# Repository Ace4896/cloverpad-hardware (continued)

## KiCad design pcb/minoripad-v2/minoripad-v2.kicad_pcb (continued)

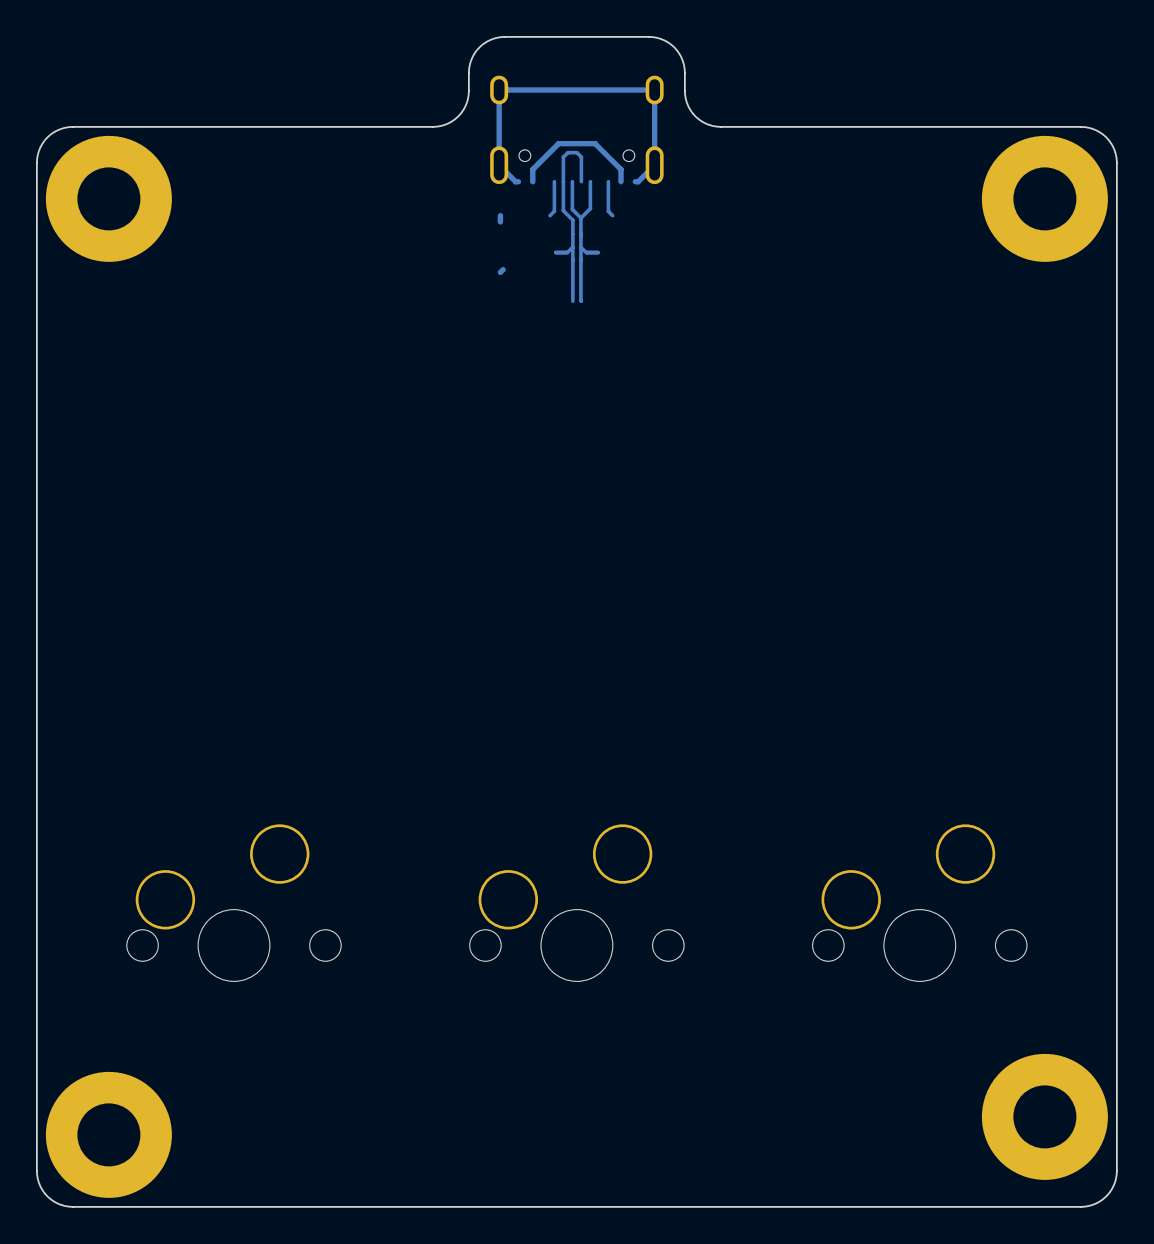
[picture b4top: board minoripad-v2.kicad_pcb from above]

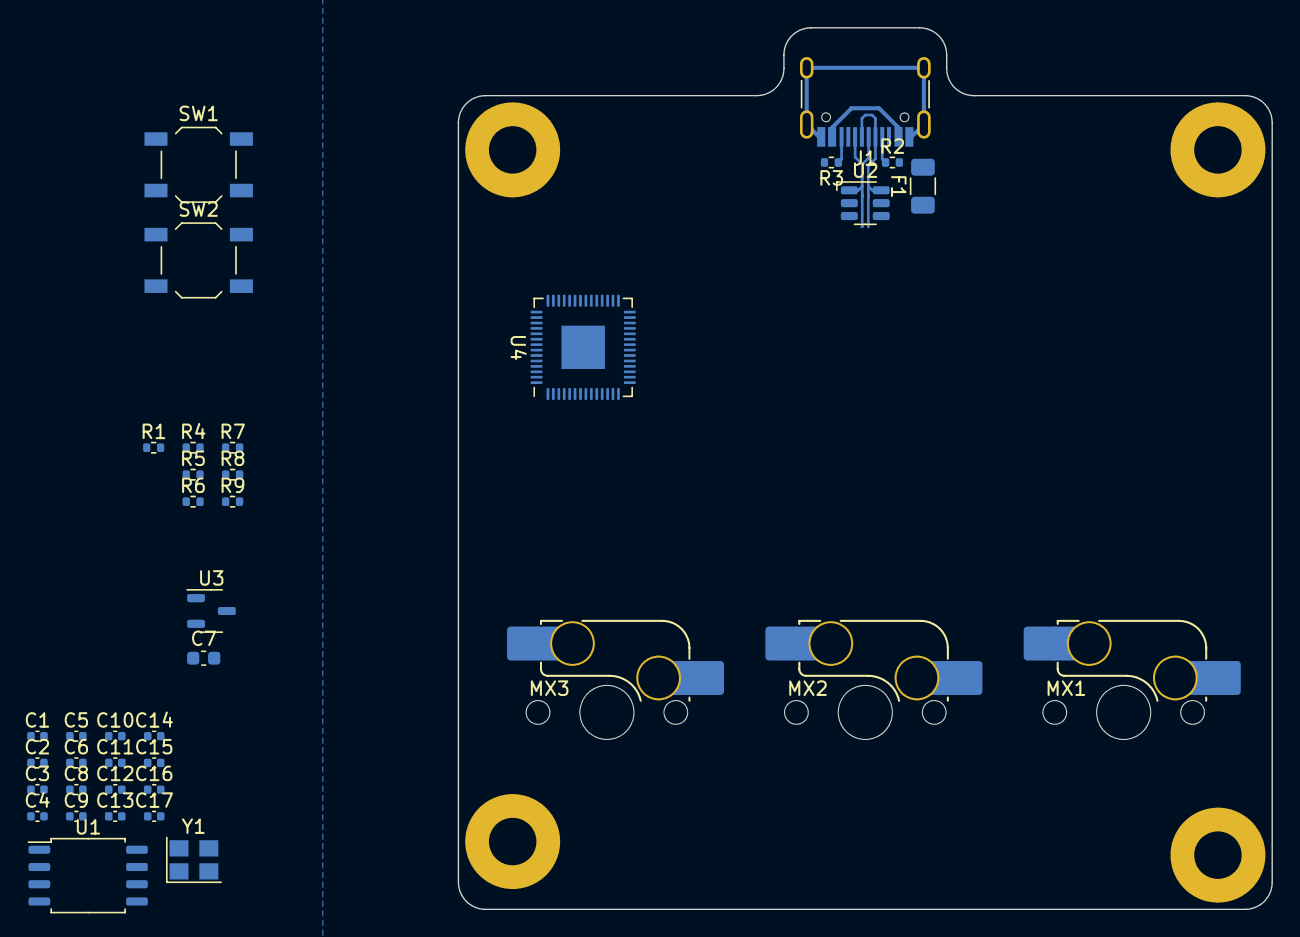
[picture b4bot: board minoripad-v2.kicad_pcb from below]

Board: 2 copper layers, 60.0 x 65.0 mm, 42 parts (42 on the bottom side), 26 nets.

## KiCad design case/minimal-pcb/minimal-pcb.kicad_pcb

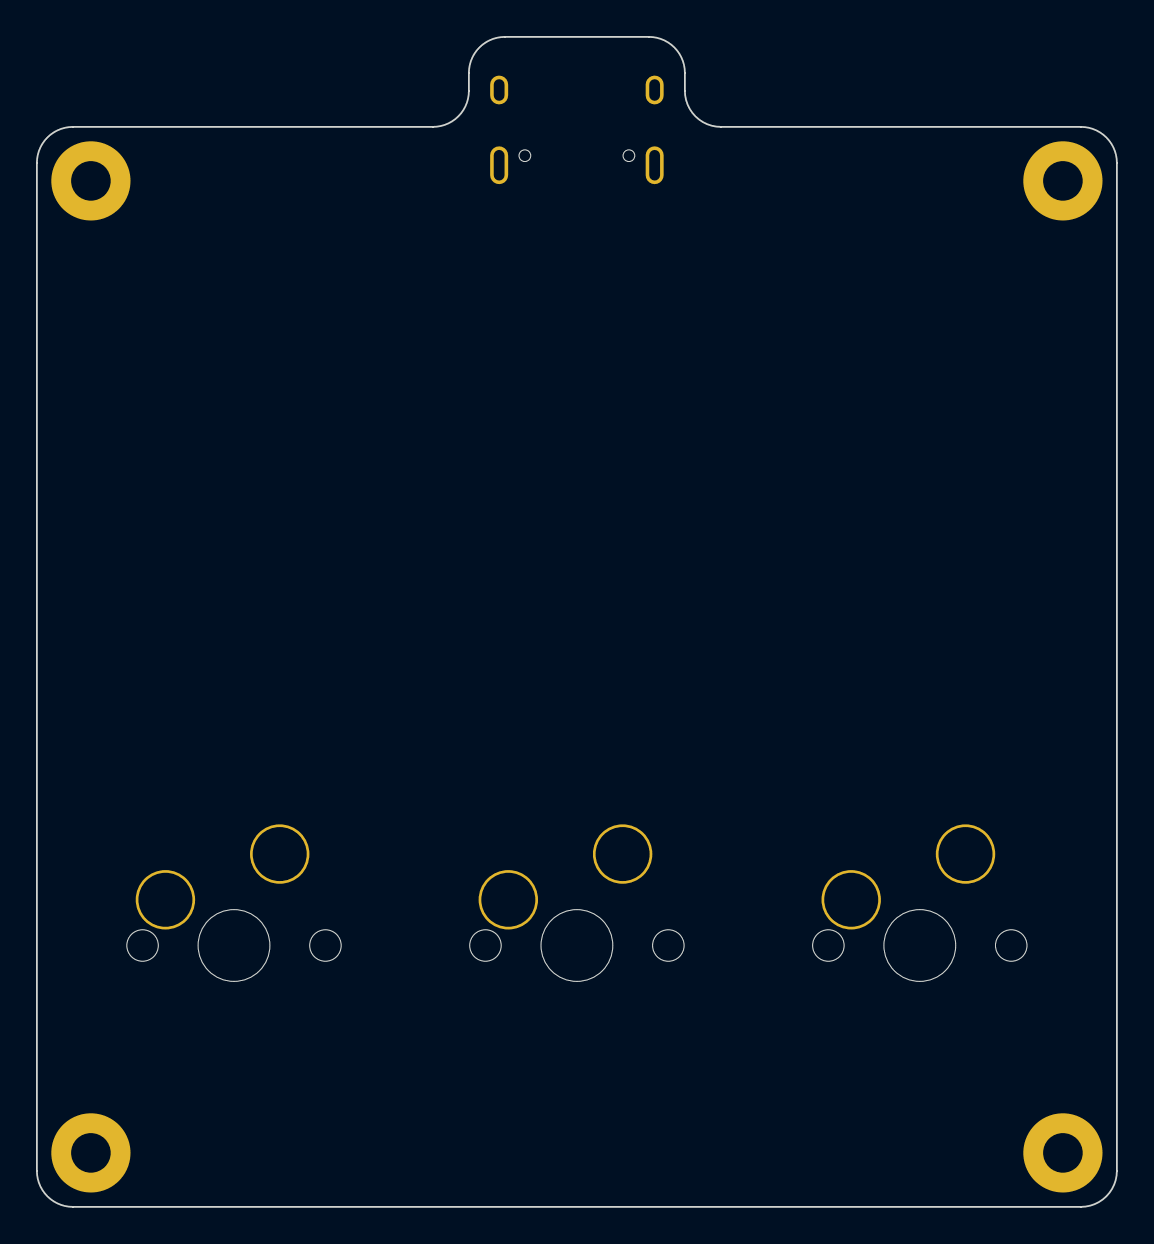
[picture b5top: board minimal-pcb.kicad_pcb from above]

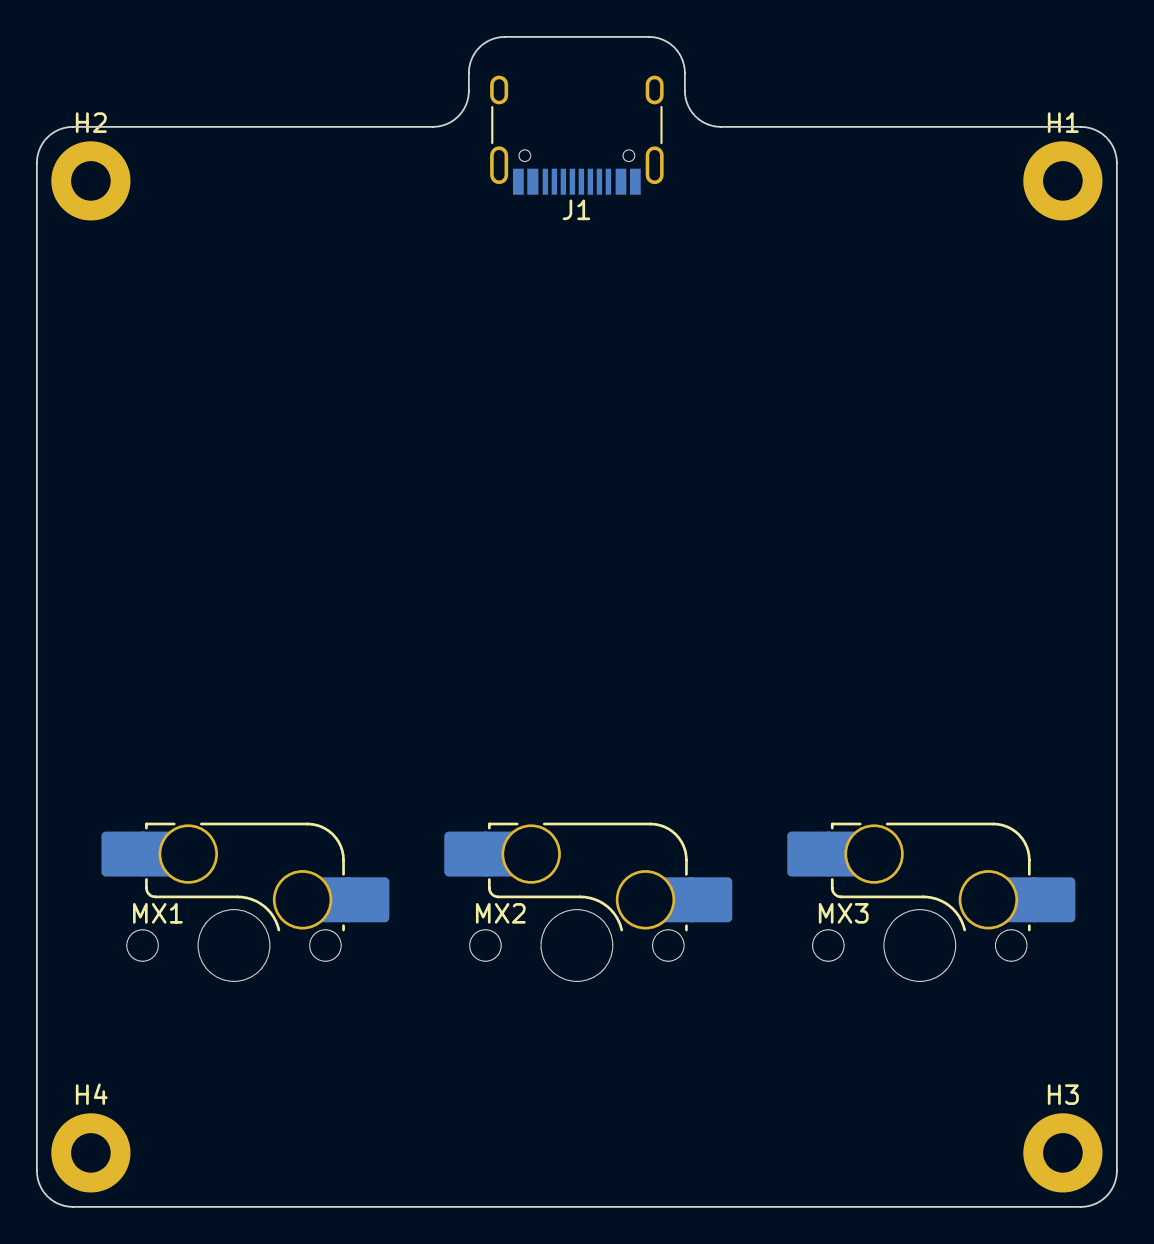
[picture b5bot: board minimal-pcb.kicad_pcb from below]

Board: 2 copper layers, 60.0 x 65.0 mm, 8 parts (8 on the bottom side), 2 nets, no tracks yet.

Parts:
H1, H2, H3, H4: Mounting Hole; MountingHole_2.2mm_M2_Pad
J1: USB_C_Receptacle_USB2.0; USB_C_Receptacle_HRO_TYPE-C-31-M-12
MX1, MX2, MX3: MX_SW_HS; SW_MX_HS_1u

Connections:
unnamed: J1.A1 (GND), J1.A12 (GND), J1.B1 (GND), J1.B12 (GND)
unnamed: J1.A4 (VBUS), J1.A9 (VBUS), J1.B4 (VBUS), J1.B9 (VBUS)

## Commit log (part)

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2023-11-05 feat: initial commit
2023-11-05 chore: add kle layout
2023-11-05 docs: add notes on lekker / ks-20 switches
2023-11-05 chore: setup kicad project for pcb
2023-11-05 docs: add datasheets for RP2040
2023-11-05 chore: add kicad symbols + footprints from previous attempt
2023-11-05 feat: initial schematic
    has the bare minimum components for a working keypad.
2023-11-05 chore: add auto saved files to gitignore
2023-11-05 feat: add rgb underglow
2023-11-05 refactor: use marbastlib footprint for in-switch LED
    to make it easier to align.
2023-11-05 feat: initial attempt at laying out pcb
    routing will be tricky - might need a 4 layer pcb due to the mixed voltages...
    probably better to remove the in-switch LEDs for the time being...
2023-11-06 docs: add labels for relevant parts
2023-11-06 fix: add 3.3v to 5v logic conversion
    this uses the 74AHCT1G125. there are values that can step up multiple pins at once, but it seems cheaper to just use individual ones. it should also be easier to route, as the logic level conversion 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
2023-11-06 feat: routing for rgb leds + logic level conversion
2023-11-07 feat: fully connected pcb
    ended up removing the debug header - I don't think these appear in production boards anyway, so should be OK.
    there's probably a better way to route the analog lines, but I couldn't come up with anything for it...
2023-11-07 feat: add m2 screw holes the footprint already takes the 4mm width of the standoffs into account, so should be OK as long as I position it correctly in CAD.
2023-11-07 chore: add title + revision to pcb design
2023-11-11 feat: add minimal pcb design for case measurements
2023-11-11 feat: export minimal pcb to step file
2023-11-11 refactor: use git submodules for mx switch 3d models (1/2)
2023-11-11 refactor: use git submodules for mx switch 3d models (2/2)
2023-11-11 docs: update README.md
2023-11-11 docs: reword repository layout
2023-11-11 fix: move switches slightly higher, to move away from screw holes
2023-11-11 docs: add the beginnings of a build guide
2023-11-11 refactor: drive switch LEDs from a single output pin
2023-11-12 feat: routing for new pcb required shuffling some components around, but this casn be accounted for in software, so it's not a big deal.
2023-11-12 refactor: re-route power and signals for switch LEDs
2023-11-13 docs: add ks-20 datasheet + notes on hall sensors
2023-11-13 feat: add haruka emote on back of pcb
2023-11-13 feat: add minori emote on front of pcb
2023-11-13 chore: add chosen emotes + splash art for pcb
2023-11-13 chore: trim source images for emotes
2023-11-13 feat: add mmj logo to front of pcb
2023-11-13 feat: wip attempt at vectorizing haruka emote
2023-11-14 chore: re-organise pcb artwork
2023-11-14 fix: fix haruka-16 emote on pcb and adjust alignment
2023-11-14 chore: remove pcb artwork for now since I want to try re-routing the PCB again.
2023-11-14 refactor: new pcb layout
    more compact and has fewer crossing lines. can definitely shrink the PCB, but I've picked this size so it's possible to see the design from the top.
2023-11-14 refactor: create custom footprint for KS-20 w/ DRV5056
    this includes a custom silkscreen, reference value and a rule area to disallow copper fills in the middle of the sensor.
2023-11-14 refactor: route +5v for underglow without crossing over analog lines
2023-11-15 chore: rename mounting holes in schematic
2023-11-15 refactor: route analog +3v3 without going underneath LEDs just realised that it may cause some noise in the supply.
2023-11-15 docs: fix typo
2023-11-15 fix: resolve all silkscreen overlaps
2023-11-15 fix: resolve footprint mismatch warnings
2023-11-15 chore: export 3d step file for pcb
    measurements look good; no issues with component clearance and the
    bottom cutouts line up with the buttons.
2023-11-15 refactor: use 1206 footprint for fuse
    there are more polyfuses with 500mA hold current at this size.
2023-11-15 feat: setup bom and initial gerbers files
2023-11-15 feat: setup jlcpcb tools
    seems to be working - the generated gerbers, bom and cpl are correct.
    the DRV5056 isn't being picked up, but it's likely just because it's out of stock.
2023-11-15 feat: add jlc order number placeholder
2023-11-15 fix: ensure that mounting holes are excluded from bom
2023-11-15 docs: fix typo in component table
2023-11-15 feat: add haruka-16 to pcb again
2023-11-15 fix: adjust linework on minori-02
2023-11-15 feat: add rest of mmj to front of pcb
2023-11-15 feat: add mmj logo to back of pcb
2023-11-15 docs: fix copy-paste error for kicad 7 link
2023-11-15 fix: add missing saved details
2023-11-16 fix: adjust ks-20 footprints so they're on front side by default
    so that when it's flipped, the components appear on the back side in the BOM. this way, it can be assembled with the rest of the components
2023-11-16 fix: convert case mounting holes to 3.5mm diameter hexagons
2023-11-16 docs: add note on hex standoff outer diameter
2023-11-17 refactor: parameterize hex standoff outer diameter
2023-11-17 docs: suggest frosted acrylic for plate
    to help the switch LED lighting diffuse a bit better.
2023-11-19 docs: fix quantity of m2 screws in build guide
2023-11-19 fix: rework clover in mmj logo
2023-11-19 chore: remove kle
    doesn't look like I'll need it - can always re-add it later.
2023-11-19 chore: re-organise folder structure
2023-11-19 docs: add link to assets folder
2023-11-20 docs: initial notes on determining magnet distance
2023-11-21 fix: another way of interpreting the ks-20 datasheet
    this gives a profile that is closer to that of the datasheet.
2023-11-21 feat: another attempt using fractional curve fitting
2023-11-21 chore: add plot titles
2023-11-28 fix: use padded 3.5mm mounting holes in minimal PCB
2023-11-28 chore: update 3d .step files for pcbs
2023-11-28 fix: use rounded 3.5mm mounting holes in case
    also use the new 3d models for the PCBs. nice to see that all of them line up now.
2023-11-28 fix: correct license for marbastlib
2023-11-28 docs: add copyright notice for MMJ
2023-11-28 docs: fix grammar in README
2023-11-28 fix: move JLC order number placeholder
    so it doesn't overlap with the pad.
2023-11-28 fix: remove remaining references to hex standoffs
2023-11-28 refactor: minify kle layout
    since this is the format that will be sent over the wire.
2023-11-28 fix: use k1, k2 and k3 in kle
    to make it more universal.
2023-11-28 fix: 0-based indexing
    to make it easier later...
2023-12-02 docs: update parts list to use DRV5056A4
2023-12-02 docs: update lcsc part number for DRV5056A4
2023-12-05 refactor: cleanup magnet-distance notebook
    makes it a bit easier to compare the different curve fits.
2023-12-22 chore: rename project
2023-12-22 feat: add minoripad
    this is a simplified version of the harukapad, with regular MX switches and no RGB effects.
    will be used to validate my case design.
2023-12-22 chore: import minoripad pcb 3d model into case project
2023-12-22 docs: expand notes on standoff outer diameter
2023-12-22 fix: correct title in minoripad schematic
2023-12-24 fix: increase size of usb-c cutout
    my constraint was placed incorrectly, so the cutout clipped into the usb-c's 3d model...
2023-12-24 fix: use south facing switches in minimal PCB
    didn't notice until I saw the positioning of the hotswap sockets on the minoripad PCB...
2023-12-24 chore: export case files to dxf and step for 3.5mm hole diameter
2024-01-13 feat: smaller pcb + case design
2024-01-13 feat: new plate design with pcb spacers
2024-01-20 feat: new bottom piece
2024-01-21 feat: 6 degree angle on case
2024-01-21 feat: mostly finished design for 3d printed case
2024-01-21 chore: remove old case files
2024-01-21 chore: update minimal pcb
    got the usb cutout dimensions wrong on the pcb... need to fix it
2024-01-21 fix: add screw holes to top piece
2024-01-21 chore: export case files for 3d printing / cnc
2024-01-21 chore: rename projects
2024-01-21 docs: laser cut acrylic -> 3d printed
2024-01-21 chore: add license info to freecad project
2024-01-26 chore: remove rgb from Cloverpad HE pcb
    I want to keep the cost down; including RGB means that standard PCB assembly is needed, which causes the price to spike...
2024-01-26 fix: use 70x70mm pcb size and 80x80mm case
    proides enough clearance all of the parts, as I've already managed to route traces this way.
2024-01-26 refactor: parameterise threaded insert height
2024-01-26 refactor: add aliases for case parameters
2024-01-26 refactor: add aliases for all parameters
2024-01-26 chore: remove foot for 6 degree angle
    not sure how will this will print if it's attached... but it's probably better if the keypad is flat anyway.
2024-01-26 fix: port pcb shape changes to cloverpad mx
2024-01-26 chore: export 3d model of cloverpad mx pcb
2024-01-26 fix: swap positions of MX1 and MX3 on cloverpad mx
    makes more sense as when viewed from the front, MX1 is the leftmost switch.
2024-01-26 fix: port pcb size changes to cloverpad he
    since there's no RGB now, it's possible to route the analog signals more directly.
2024-01-26 chore: export 3d model of cloverpad he pcb
2024-01-26 docs: update repository link in README
2024-01-26 fix: normalise position of JLC order number on PCB
2024-01-27 refactor: simplify pcb mounting holes on bottom piece
    less material used, so it's cheaper to print.
2024-01-27 fix: adjust case design based on final parts list
2024-01-27 fix: add rotations for cloverpad mx
2024-01-27 fix: increase case size slightly
    if the top half is slightly too small and the pcb is slightly too large, the case won't fit together...
2024-02-04 feat: curve fitting magnet distance in micrometres
2024-02-04 feat: print expected adc values for top/bottom positions
2024-02-04 feat: add maximum adc value for drv5056
2024-02-05 chore: mark case/pcb files as rev1, since I've produced them already
2024-02-06 chore: re-organise files into top-level rev1/rev2 folder
2024-02-06 docs: add README for rev 1
2024-02-06 docs: add list of required parts (for reference)
2024-02-06 docs: add photos of rev 1 case + pcb
2024-02-06 chore: copy rev. 1 files to rev. 2
2024-02-09 docs: add note about rev. 1 pcb that wouldn't boot into flashed firmware
2024-02-24 chore: upgrade all pcb projects to KiCad 8
2024-03-03 chore: update all symbols + footprints to match kicad 8
2024-03-04 chore: remove chibi emotes from Cloverpad HE pcb
    they're unlikely to be recognisable at that size - only a few
    millimetres wide...
2024-03-10 chore: change project uuid for rev 2 case
2024-05-14 feat: initial attempt at stm32-based schematic for Cloverpad MX
    very messy schematic - need to tidy it up and double check parts before attempting to route it.
    the PCB is essentially the same for Cloverpad HE - just replace the hotswap sockets for the DRV5056 (+ filtering)
2024-05-15 refactor: tidy up rev2-stm32 schematic
2024-05-15 refactor: re-annotate components on rev2-stm32 PCB
2024-05-26 refactor: swap f072 with f401 has higher performance and on JLC, it doesn't cost much more. will need this for the ADC functionality later
2024-06-08 chore: add rp pico datasheet
2024-06-09 docs: add LM4040 and SS39ET datasheets
2024-06-09 docs: fix typo in rev. 1 readme
2024-06-09 feat: initial attempt at new case
    shrinking it is a bit difficult without knowing what's on the PCB - need to make sure I can route this...
    probably better to design the PCB first so I know what the minimum size is.
2024-06-09 feat: add external AT24C32 EEPROM
    for 3.3V, it seems that anything from 2k to 4.7k will work, but I've seen 10k working on Adafruit's EEPROM breakout. I've chosen 5.1k to minimise the BOM (the same ones used for USB).
